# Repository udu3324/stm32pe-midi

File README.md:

# stm32pe-midi controller

An expressive midi controller based on the stm32 ecosystem. It uses the MPE midi protocol to pass through signals that act as gestures/effects including velocity/note to any music DAW. (like ableton)

 - Uses the powerful STM32H7
 - Uses USB-C OTG to connect to a device
 - Has per key PWM leds for indication
 - Low profile/one sided pcb design
 - Small key footprint for compactness
 - Two octaves + extra key before an octave

See it in action [here](https://www.youtube.com/watch?v=022ZFJn4nkc)!

# Why I Made It

This controller will be able to make music more accessible by being more affordable to the typical person. Most MPE midi controllers on the market cost between [$500 USD to $2000](https://www.expressivee.com/2-osmose). I also made this project to touch the stm32 ecosystem and learn how to integrate and use it. This midi keyboard could also make my workflow nicer for making music in Ableton.

# Design

To reduce the cost of production, I decided to design a compliant mechanism (flexure) that would be only one part. It would reduce the labor and cost by a lot. This is because most keyboards/pianos have between 10 to 100 which I have reduced to a minimum of 2. A hall effect sensor is used to measure the position and rotation of a magnet embedded in each key.

# Problems

There were many problems while prototyping and laying out things. I had bare knowledge of how flexures worked and had to create as many prototypes as needed until the right movement was made. I also didn't know that the size of the board would be a big constraint that was completely ignored.

**I highly recommend to look over these issues before building another stm32pe device!!!**
A lot of tolerances for the 3d prints are based on my 3d-printer. Make sure to print segments before making the entire thing to test for fit between the pcb, magnet, and everything.

Problems during fabrication
 * TMAG5273 has a fixed i2c address which only differs by buying different models (B1, C1, D1) or by running extra interrupt traces
 * M screw spacers broke off when screwing into plastic
 * Too high of a tolerance between the board and 3d printed parts, had to cut off bottom two aligners on all keys
 * Connection (led mux) from main-board to other board was made through really tiny & painful to solder wires

Here's a list of problems after fabrication + firmware
 * The Black key flexure design suffers too much with plastic deformation permanently, as well as temporarily
 * ^ This issue also causes a permanent distance change with less distance to measure and use
 * TMAG5273 library has no calibration feature and the measured angle is offset when brought closer
 * Keys are a bit too slippery and need a dimple to grip the finger
 * Flexures on both key types are a little on the firm side, takes a little time to get used to
 * Last white key (b) is impractical as header wires are blocking its roll to pitch change up
 * The power on led is a bit too bright, not changeable
 * The base/case of the stm32h7 is kinda slippery
 * PLA flexures can get deformed under heat in a car which can leave a permanent loss of height on keys or mess more with the already high tolerance to allow press fitting

These issues do not make the stm32pe midi keyboard worthless or horrible to use, but are just little tiny problems that could be polished in the future.

# Firmware

 * [tinyusb lib](https://github.com/hathach/tinyusb) on MIT license
 * [i2c-mux stm32 lib](https://github.com/jtainer/i2c-mux) on BSD-2-Clause license
 * [stm32 tmag5273 lib](https://github.com/devOramaMan/stm32_TMAG5273) on No license (added a i2c address rewrite based on the datasheet as well as a crucial fix)

Thank you to all the open source libraries above to make this project possible. I don't think I would have the expertise to implement all my ics this well.

The firmware for the stm32pe midi controller is written in c/cpp on stm32cubeide and flashed with stm32cubeprogrammer. Amazing platform. Outdated UI (lol). **To be as transparent as possible**, some of the firmware was written/assisted with AI. About 20% of it was written mostly with AI, while the rest + logic that ties everything together was me. `mpe.c`, 80% of `helper.c`, 60% of `tlc5940.c`, and 5% of `main.c` with some fixes to `TMAG5273.c` was assisted with AI. I do understand what the firmware does. Depending on your perspective on AI, it shouldn't really matter as I know what I'm doing. 

All of the code is stored in `firmware/stm32pe_midi/Core/Src` or `/Core/Inc`. `Src/main.c` contains some user preferences that can be set through variables.

```c
//midi
int start_octave = 4; //midi code shift
int mt_send_black = 40; //midi on threshold
int mt_send_white = 30; //midi on threshold

//mpe
int16_t pitch_mpe_st = 682; //mpe semitone pitch range (682 = 4st, 341 = 2st)
float angle_mpe_padding = 15; //mpe pitch
float angle_mpe_realistic_max = 25; //mpe pitch

float aftertouch_mpe_white_padding = 9; //mpe aftertouch
float aftertouch_mpe_black_padding = 15; //mpe aftertouch

//octave
uint32_t octave_change_mode_time_threshold = 200; //diff change between mode/octive
uint32_t octave_led_flash = 500; //ms between led flash during mode

//led
int startup_cutoff_wait = 100; //led cutoff + cutoff for initial sensor readings saving

//mode
uint32_t octave_mode_hold_down = 1500; //octave mode keys milliseconds to hold down & change
uint32_t mpe_mode_hold_down = 3000; //~ same above but for mpe mode keys

//debug
bool disable_comport = false; //silences comport to possibly make processing faster?
```

# Wiring

# BOM
This is an approximate bill of materials that is a little flexible. It would be around $333.27, ±5 dollars in case of shipping or extra taxes/fees. Thank you Hack Club - Highway for funding this.

| Part                       | Cost         | Count | Supplier | Note                                                           | Link                                                                                            |
|----------------------------|--------------|-------|----------|----------------------------------------------------------------|-------------------------------------------------------------------------------------------------|
| PLA Filament (white)       | $16.99       | 1     | Amazon   | I have a 3d printer and would like to print most of the parts. | [https://www.amazon.com/dp/B07PGZNM34](https://www.amazon.com/dp/B07PGZNM34)                    |
| PLA Filament (black)       | $16.99       | 1     | Amazon   | ~ (for the black keys)                                         | [https://www.amazon.com/dp/B07PGY2JP1](https://www.amazon.com/dp/B07PGY2JP1)                    |
| UV Plastic Glue            | $14.15       | 1     | Amazon   | This is for the underside of the keys to stop scraping.        | [https://www.amazon.com/dp/B00QU5M4VW](https://www.amazon.com/dp/B00QU5M4VW)                    |
| Header 10 Pins             | $0.78        | 2     | DigiKey  | (does not include shipping/taxes)                              | [68000-110HLF](https://www.digikey.com/en/products/detail/amphenol-cs-fci/68000-110HLF/1878503) |
| Header 5 Pins              | $0.63        | 1     | DigiKey  | ~                                                              | [68000-105HLF](https://www.digikey.com/en/products/detail/amphenol-cs-fci/68000-105HLF/2023304) |
| PCB Fabrication + Assembly | $151.09      | 2     | JLCPCB   | *no coupons applied yet                                        |                                                                                                 |
| PCB Shipping               | $33.52       | n/a   | ~        |                                                                |                                                                                                 |
| Customs duties & taxes     | $83.10       | n/a   | ~        |                                                                |                                                                                                 |
| Sales Tax                  | $15.24       | n/a   | ~        |                                                                |                                                                                                 |
| TOTAL                      | $333.27      |       |          |                                                                |                                                                                                 |

I forgot to add two more parts to the bom. They have been covered out of pocket which is fine

| Part                  | Cost    | Count | Supplier | Note                                                                                                                                                         | Link                                                                                                         |
|-----------------------|---------|-------|----------|--------------------------------------------------------------------------------------------------------------------------------------------------------------|--------------------------------------------------------------------------------------------------------------|
| 5mm Cube Magnets      | $16.99  | 45    | Amazon   | I could not find any listings with lower quantities                                                                                                          | [https://www.amazon.com/dp/B0CW9GVTX2](https://www.amazon.com/dp/B0CW9GVTX2)                                 |
| M3 5mm Screws         | ¥2.14   | 50    | Taobao   | Pretty cheap! (30 cents usd)                                                                                                                                 | [https://detail.tmall.com/item.htm?id=722759297726](https://detail.tmall.com/item.htm?id=722759297726)       |
| Female 10pin Headers  | $5.62   | 1     | Mouser   | This is for the main board. The part itself **costs $0.63 without taxes/shipping.**                                                                          | [https://www.mouser.com/ProductDetail/710-61301011821](https://www.mouser.com/ProductDetail/710-61301011821) |
| JLCPCB Two Design Fee | $38.99  | n/a   | JLCPCB   | 😭 i did not think about this while designing, i tried negotiating and doing everything                                                                      |                                                                                                              |
| TMAG5273-B1/C1/D1     | $23.28  | 18    | Mouser   | i stg the datasheet said the sensor's i2c addresses were reprogrammable.. but they didn't say i needed to hookup interrupts to them too... lesson learned :p |                                                                                                              |
| Total out of pocket   | $85.18  |       |          |                                                                                                                                                              |                                                                                                              |
| REAL TOTAL            | $418.45 |       |          |                                                                                                                                                              |                                                                                                              |

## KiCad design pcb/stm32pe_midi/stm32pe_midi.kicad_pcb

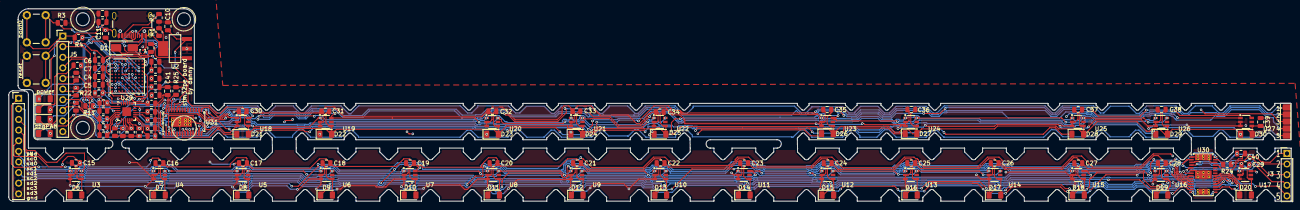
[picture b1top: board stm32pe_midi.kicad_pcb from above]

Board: 4 copper layers, 307.0 x 46.1 mm, 135 parts (0 on the bottom side), 83 nets.

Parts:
C1, C2: 2.2μF; C_0805_2012Metric
C3, C5: 4.7μF; C_0805_2012Metric
C4, C6, C7, C9, C12: 100nF; C_0805_2012Metric
C8, C13, C14: 1μF; C_0805_2012Metric
C10: 33μF; C_0805_2012Metric
C11: 0.47μF; C_0805_2012Metric
C15, C16, C17, C18, C19, C20, C21, C22, C23, C24, C25, C26, C27, C28, C29, C30, C31, C32, C33, C34, C35, C36, C37, C38, C39, C40, C41: 0.1μF; C_0805_2012Metric
D1: SS14; D_SMA
D3, D4, D5, D33: LED; LED_1206_3216Metric
D6, D7, D8, D9, D10, D11, D12, D13, D14, D15, D16, D17, D18, D19, D20, D21, D22, D23, D24, D25, D26, D27, D28, D29, D30: LED_Small; LED_1206_3216Metric
J1: USB4105; USB_C_Receptacle_GCT_USB4105-xx-A_16P_TopMnt_Horizontal
J3: Conn_01x05_Pin; PinHeader_1x05_P2.54mm_Vertical
J4: Conn_01x10_Pin; PinHeader_1x10_P2.54mm_Vertical
J5: Conn_01x10_Socket; PinHeader_1x10_P2.54mm_Vertical
J6: Conn_01x05_Pin; custom_pads
R1, R2, R24, R25: 5.1kΩ; R_0805_2012Metric
R3, R4: 10kΩ; R_0805_2012Metric
R5, R6, R7, R27: 330Ω; R_0805_2012Metric
R8, R9, R10, R11, R12, R13, R14, R15, R16, R17, R18, R19, R20, R21, R22, R23: 2.2kΩ; R_0805_2012Metric
SW1, SW2: SW_SPST; SW_PUSH_6mm
U1: STM32H743VIHx; TFBGA-100_8x8mm_Layout10x10_P0.8mm
U2: LM3940IMPX-3.3/NOPB; SOT-223-4_L6.5-W3.5-P2.30-LS7.0-BR
U3, U4, U5, U6, U7, U8, U9, U10, U11, U12, U13, U14, U15, U16, U17, U18, U19, U20, U21, U22, U23, U24, U25, U26, U27: TMAG5273; SOT-23-6_L2.9-W1.6-P0.95-LS2.8-BR
U28: TPD2EUSB30; Texas_DRT-3
U29: TCA9548A; Texas_RGE0024C_VQFN-24-1EP_4x4mm_P0.5mm_EP2.1x2.1mm
U30, U31: TLC5940PWP; HTSSOP-28-1EP_4.4x9.7mm_P0.65mm_EP3.4x9.5mm_Mask2.4x6.17mm_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

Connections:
3v3: C4.2, C5.2, C6.2, C7.2, C10.1, C12.1, C13.1, C15.2, C16.2, C17.2, C18.2, C19.2, C20.2, C21.2, C22.2, C23.2, C24.2, C25.2, C26.2, C27.2, C28.2, C29.2, C30.2, C31.2, C32.2, C33.2, C34.2, C35.2, C36.2, C37.2, C38.2, C39.2, C40.2, C41.2, D3.2 (A), D6.2 (A), D7.2 (A), D8.2 (A), D9.2 (A), D10.2 (A), D11.2 (A), D12.2 (A), D13.2 (A), D14.2 (A), D15.2 (A), D16.2 (A), D17.2 (A), D18.2 (A), D19.2 (A), D20.2 (A), D21.2 (A), D22.2 (A), D23.2 (A), D24.2 (A), D25.2 (A), D26.2 (A), D27.2 (A), D28.2 (A), D29.2 (A), D30.2 (A), J4.1, J5.1, R4.1, R8.2, R9.2, R10.2, R11.2, R12.2, R13.2, R14.2, R15.2, R16.2, R17.2, R18.2, R19.2, R20.2, R21.2, R22.2, R23.2, SW1.2 (B), U1.B2 (VBAT), U1.D2 (VDD), U1.F5 (VDD), U1.F6 (VDD33_USB), U1.K1 (VDD), U2.3 (OUT), U3.4 (VCC), U4.4 (VCC), U5.4 (VCC), U6.4 (VCC), U7.4 (VCC), U8.4 (VCC), U9.4 (VCC), U10.4 (VCC), U11.4 (VCC), U12.4 (VCC), U13.4 (VCC), U14.4 (VCC), U15.4 (VCC), U16.4 (VCC), U17.4 (VCC), U18.4 (VCC), U19.4 (VCC), U20.4 (VCC), U21.4 (VCC), U22.4 (VCC), U23.4 (VCC), U24.4 (VCC), U25.4 (VCC), U26.4 (VCC), U27.4 (VCC), U29.21 (VCC), U30.28 (VCC), U31.28 (VCC)
5v: C11.1, C14.2, U2.1 (IN)
BLANK: J6.2, U1.K2 (PA3), U31.2 (BLANK)
BOOT0: R3.2, SW1.1 (A), U1.D5 (BOOT0)
GND: C1.1, C2.1, C3.1, C4.1, C5.1, C6.1, C7.1, C8.1, C9.1, C10.2, C11.2, C12.2, C13.2, C15.1, C16.1, C17.1, C18.1, C19.1, C20.1, C21.1, C22.1, C23.1, C24.1, C25.1, C26.1, C27.1, C28.1, C29.1, C30.1, C31.1, C32.1, C33.1, C34.1, C35.1, C36.1, C37.1, C38.1, C39.1, C40.1, C41.1, J1.A1 (GND), J1.A12 (GND), J1.B1 (GND), J1.B12 (GND), J1.S1 (SHIELD), J4.10, J5.10, R1.2, R2.1, R3.1, R5.1, R6.1, R7.1, R24.1, R25.1, R27.1, SW2.2 (B), U1.C2 (VSS), U1.E4 (VSS), U1.E5 (VSS), U1.E6 (VSS), U1.G1 (VSSA), U1.J1 (VSS), U2.2 (GND), U2.4 (GND), U3.2 (GND), U3.3 (GND(TEST)), U4.2 (GND), U4.3 (GND(TEST)), U5.2 (GND), U5.3 (GND(TEST)), U6.2 (GND), U6.3 (GND(TEST)), U7.2 (GND), U7.3 (GND(TEST)), U8.2 (GND), U8.3 (GND(TEST)), U9.2 (GND), U9.3 (GND(TEST)), U10.2 (GND), U10.3 (GND(TEST)), U11.2 (GND), U11.3 (GND(TEST)), U12.2 (GND), U12.3 (GND(TEST)), U13.2 (GND), U13.3 (GND(TEST)), U14.2 (GND), U14.3 (GND(TEST)), U15.2 (GND), U15.3 (GND(TEST)), U16.2 (GND), U16.3 (GND(TEST)), U17.2 (GND), U17.3 (GND(TEST)), U18.2 (GND), U18.3 (GND(TEST)), U19.2 (GND), U19.3 (GND(TEST)), U20.2 (GND), U20.3 (GND(TEST)), U21.2 (GND), U21.3 (GND(TEST)), U22.2 (GND), U22.3 (GND(TEST)), U23.2 (GND), U23.3 (GND(TEST)), U24.2 (GND), U24.3 (GND(TEST)), U25.2 (GND), U25.3 (GND(TEST)), U26.2 (GND), U26.3 (GND(TEST)), U27.2 (GND), U27.3 (GND(TEST)), U28.3 (GND), U29.9 (GND), U29.18 (A2), U29.22 (A0), U29.23 (A1), U30.1 (GND), U30.6 (VPRG), U30.26 (DCPRG), U30.29 (PAD), U31.1 (GND), U31.6 (VPRG), U31.26 (DCPRG), U31.29 (PAD)
GSCLK: J6.1, U1.H2 (PA1), U31.25 (GSCLK)
I2C1_SCL: R23.1, U1.B5 (PB6), U29.19 (SCL)
I2C1_SDA: R22.1, U1.A5 (PB7), U29.20 (SDA)
MPRESET: U1.B4 (PB8), U29.24 (~RESET)
NRST: R4.2, SW2.1 (A), U1.E1 (NRST)
unnamed: C1.2, U1.E7 (VCAP)
unnamed: C2.2, U1.F8 (VCAP)
unnamed: D1.2 (A), J1.A4 (VBUS), J1.A9 (VBUS), J1.B4 (VBUS), J1.B9 (VBUS)
unnamed: C14.1, D1.1 (K)
unnamed: D3.1 (K), R5.2
unnamed: D4.1 (K), R6.2
unnamed: D5.1 (K), R7.2
unnamed: D6.1 (K), U30.7 (OUT0)
unnamed: D7.1 (K), U30.8 (OUT1)
unnamed: D8.1 (K), U30.9 (OUT2)
unnamed: D9.1 (K), U30.10 (OUT3)
unnamed: D10.1 (K), U30.11 (OUT4)
unnamed: D11.1 (K), U30.12 (OUT5)
unnamed: D12.1 (K), U30.13 (OUT6)
unnamed: D13.1 (K), U30.14 (OUT7)
unnamed: D14.1 (K), U30.15 (OUT8)
unnamed: D15.1 (K), U30.16 (OUT9)
unnamed: D16.1 (K), U30.17 (OUT10)
unnamed: D17.1 (K), U30.18 (OUT11)
unnamed: D18.1 (K), U30.19 (OUT12)
unnamed: D19.1 (K), U30.20 (OUT13)
unnamed: D20.1 (K), U30.21 (OUT14)
unnamed: D21.1 (K), U31.7 (OUT0)
unnamed: D22.1 (K), U31.8 (OUT1)
unnamed: D23.1 (K), U31.9 (OUT2)
unnamed: D24.1 (K), U31.10 (OUT3)
unnamed: D25.1 (K), U31.11 (OUT4)
unnamed: D26.1 (K), U31.12 (OUT5)
unnamed: D27.1 (K), U31.13 (OUT6)
unnamed: D28.1 (K), U31.14 (OUT7)
unnamed: D29.1 (K), U31.15 (OUT8)
unnamed: D30.1 (K), U31.16 (OUT9)
unnamed: D33.1 (K), R27.2
unnamed: J1.A5 (CC1), R1.1
unnamed: J1.B5 (CC2), R2.2
unnamed: J3.1, U30.25 (GSCLK)
unnamed: J3.2, U30.2 (BLANK)
unnamed: J3.3, U30.3 (XLAT)
unnamed: J3.4, U30.4 (SCLK)
unnamed: J3.5, U30.5 (SIN)
unnamed: J5.2, R9.1, U29.2 (SC0)
unnamed: J5.3, R8.1, U29.1 (SD0)
unnamed: J5.4, R10.1, U29.4 (SC1)
unnamed: J5.5, R11.1, U29.3 (SD1)
unnamed: J5.6, R12.1, U29.6 (SC2)
unnamed: J5.7, R13.1, U29.5 (SD2)
unnamed: J6.5, U31.24 (SOUT)
unnamed: C8.2, C9.2, U1.H1 (VDDA)
unnamed: C3.2, U1.F4 (VDDLDO)
unnamed: R24.2, U30.27 (IREF)
unnamed: R25.2, U31.27 (IREF)
OTG_FS_DM: J1.A7 (D-), J1.B7 (D-), U1.C10 (PA11), U28.2 (D-)
OTG_FS_DP: J1.A6 (D+), J1.B6 (D+), U1.B10 (PA12), U28.1 (D+)
PA8: D33.2 (A), U1.D9 (PA8)
SC0: J4.2, U3.1 (SCL), U4.1 (SCL), U5.1 (SCL), U6.1 (SCL)
SC1: J4.4, U7.1 (SCL), U8.1 (SCL), U9.1 (SCL), U10.1 (SCL)
SC2: J4.6, U11.1 (SCL), U12.1 (SCL), U13.1 (SCL), U14.1 (SCL)
SC3: J4.8, J5.8, R14.1, U15.1 (SCL), U16.1 (SCL), U17.1 (SCL), U18.1 (SCL), U29.8 (SC3)
SC4: R16.1, U19.1 (SCL), U20.1 (SCL), U21.1 (SCL), U22.1 (SCL), U29.11 (SC4)
SC5: R18.1, U23.1 (SCL), U24.1 (SCL), U25.1 (SCL), U26.1 (SCL), U29.13 (SC5)
SC6: R20.1, U27.1 (SCL), U29.15 (SC6)
SCLK: J6.4, U1.H3 (PA5), U31.4 (SCLK)
SD0: J4.3, U3.6 (SDA), U4.6 (SDA), U5.6 (SDA), U6.6 (SDA)
SD1: J4.5, U7.6 (SDA), U8.6 (SDA), U9.6 (SDA), U10.6 (SDA)
SD2: J4.7, U11.6 (SDA), U12.6 (SDA), U13.6 (SDA), U14.6 (SDA)
SD3: J4.9, J5.9, R15.1, U15.6 (SDA), U16.6 (SDA), U17.6 (SDA), U18.6 (SDA), U29.7 (SD3)
SD4: R17.1, U19.6 (SDA), U20.6 (SDA), U21.6 (SDA), U22.6 (SDA), U29.10 (SD4)
SD5: R19.1, U23.6 (SDA), U24.6 (SDA), U25.6 (SDA), U26.6 (SDA), U29.12 (SD5)
SD6: R21.1, U27.6 (SDA), U29.14 (SD6)
SIN: U1.K3 (PA7), U31.5 (SIN)
USART1_RX: D5.2 (A), U1.D10 (PA10)
USART1_TX: D4.2 (A), U1.C9 (PA9)
XLAT: J6.3, U1.J2 (PA2), U31.3 (XLAT)

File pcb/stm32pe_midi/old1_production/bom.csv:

Designator,Footprint,Quantity,Value,LCSC Part #
"C1, C2",0805,2,2.2μF,
C10,0805,1,33μF,
C11,0805,1,0.47μF,
"C12, C4, C6, C7, C9",0805,5,100nF,
"C13, C14, C8",0805,3,1μF,
"C15, C16, C17, C18, C19, C20, C21, C22, C23, C24, C25, C26, C27, C28, C29, C30, C31, C32, C33, C34, C35, C36, C37, C38, C39, C40, C41",0805,27,0.1μF,
"C3, C5",0805,2,4.7μF,
D1,D_SMA,1,SS14,
"D10, D11, D12, D13, D14, D15, D16, D17, D18, D19, D20, D21, D22, D23, D24, D25, D26, D27, D28, D29, D30, D6, D7, D8, D9",1206,25,LED_Small,
D2,D_SOD-882,1,PESD5V0S1UL,
"D3, D33, D4, D5",1206,4,LED,
J1,USB_C_Receptacle_GCT_USB4105-xx-A_16P_TopMnt_Horizontal,1,USB_C_Receptacle_USB2.0_16P,
J3,PinHeader_1x05_P2.54mm_Vertical,1,Conn_01x05_Pin,
J4,PinHeader_1x10_P2.54mm_Vertical,1,Conn_01x10_Pin,
J5,PinHeader_1x10_P2.54mm_Vertical,1,Conn_01x10_Socket,
J6,custom_pads,1,Conn_01x05_Pin,
"MOUSE-BITE-2MM-SLOT-1, MOUSE-BITE-2MM-SLOT-2, MOUSE-BITE-2MM-SLOT-3, MOUSE-BITE-2MM-SLOT-4, MOUSE-BITE-2MM-SLOT-5",mouse-bite-2mm-slot,5,VAL**,
"R1, R2, R24, R25",0805,4,5.1kΩ,
"R10, R11, R12, R13, R14, R15, R16, R17, R18, R19, R20, R21, R22, R23, R8, R9",0805,16,2.2kΩ,
"R27, R5, R6, R7",0805,4,330Ω,
"R3, R4",0805,2,10kΩ,
"SW1, SW2",SW_PUSH_6mm,2,SW_SPST,
U1,TFBGA-100_8x8mm_Layout10x10_P0.8mm,1,STM32H743VIHx,
"U10, U11, U12, U13, U14, U15, U16, U17, U18, U19, U20, U21, U22, U23, U24, U25, U26, U27, U3, U4, U5, U6, U7, U8, U9",SOT-23-6_L2.9-W1.6-P0.95-LS2.8-BR,25,TMAG5273,C3716049
U2,SOT-223-4_L6.5-W3.5-P2.30-LS7.0-BR,1,LM3940IMPX-3.3/NOPB,C544820
U28,Texas_DRT-3,1,TPD2EUSB30,
U29,Texas_RGE0024C_VQFN-24-1EP_4x4mm_P0.5mm_EP2.1x2.1mm,1,TCA9548A,
"U30, U31",HTSSOP-28-1EP_4.4x9.7mm_P0.65mm_EP3.4x9.5mm_Mask2.4x6.17mm_ThermalVias,2,TLC5940PWP,

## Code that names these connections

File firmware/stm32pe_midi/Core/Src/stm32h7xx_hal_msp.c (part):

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
    __HAL_RCC_GPIOB_CLK_ENABLE();
    /**I2C1 GPIO Configuration
    PB7     ------> I2C1_SDA
    PB6     ------> I2C1_SCL
    */
    GPIO_InitStruct.Pin = GPIO_PIN_7|GPIO_PIN_6;
    GPIO_InitStruct.Mode = GPIO_MODE_AF_OD;
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    __HAL_RCC_I2C1_CLK_DISABLE();

    /**I2C1 GPIO Configuration
    PB7     ------> I2C1_SDA
    PB6     ------> I2C1_SCL
    */
    HAL_GPIO_DeInit(GPIOB, GPIO_PIN_7);

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
    __HAL_RCC_GPIOA_CLK_ENABLE();
    /**SPI1 GPIO Configuration
    PA5     ------> SPI1_SCK
    PA7     ------> SPI1_MOSI
    */
    GPIO_InitStruct.Pin = GPIO_PIN_5|GPIO_PIN_7;
    GPIO_InitStruct.Mode = GPIO_MODE_AF_PP;
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    __HAL_RCC_SPI1_CLK_DISABLE();

    /**SPI1 GPIO Configuration
    PA5     ------> SPI1_SCK
    PA7     ------> SPI1_MOSI
    */
    HAL_GPIO_DeInit(GPIOA, GPIO_PIN_5|GPIO_PIN_7);

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
    __HAL_RCC_GPIOA_CLK_ENABLE();
    /**TIM2 GPIO Configuration
    PA1     ------> TIM2_CH2
    */
    GPIO_InitStruct.Pin = GPIO_PIN_1;
    GPIO_InitStruct.Mode = GPIO_MODE_AF_PP;
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
    __HAL_RCC_GPIOA_CLK_ENABLE();
    /**USB_OTG_FS GPIO Configuration
    PA12     ------> USB_OTG_FS_DP
    PA11     ------> USB_OTG_FS_DM
    */
    GPIO_InitStruct.Pin = GPIO_PIN_12|GPIO_PIN_11;
    GPIO_InitStruct.Mode = GPIO_MODE_AF_PP;
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    __HAL_RCC_USB_OTG_FS_CLK_DISABLE();

    /**USB_OTG_FS GPIO Configuration
    PA12     ------> USB_OTG_FS_DP
    PA11     ------> USB_OTG_FS_DM
    */
    HAL_GPIO_DeInit(GPIOA, GPIO_PIN_12|GPIO_PIN_11);

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
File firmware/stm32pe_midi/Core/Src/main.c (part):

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/* Private user code ---------------------------------------------------------*/
/* USER CODE BEGIN 0 */

i2c_mux_t tca_mux = { .hi2c = &hi2c1,     // Using I2C1 on PB6 (SCL) / PB7 (SDA)
		.rst_port = GPIOB,          // Reset pin is PB7
		.rst_pin = GPIO_PIN_8,      // Use correct GPIO pin number
		.addr_offset = 0            // 0 if all A0/A1/A2 pins are GND
		};
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  HAL_GPIO_WritePin(GPIOA, GPIO_PIN_9|GPIO_PIN_8|GPIO_PIN_10|GPIO_PIN_2
                          |GPIO_PIN_3, GPIO_PIN_RESET);

  /*Configure GPIO pin : PB8 */
  GPIO_InitStruct.Pin = GPIO_PIN_8;
  GPIO_InitStruct.Mode = GPIO_MODE_OUTPUT_PP;
  GPIO_InitStruct.Pull = GPIO_NOPULL;
  GPIO_InitStruct.Speed = GPIO_SPEED_FREQ_LOW;
  HAL_GPIO_Init(GPIOB, &GPIO_InitStruct);

  /*Configure GPIO pins : PA9 PA8 PA10 PA2
                           PA3 */
  GPIO_InitStruct.Pin = GPIO_PIN_9|GPIO_PIN_8|GPIO_PIN_10|GPIO_PIN_2
                          |GPIO_PIN_3;
  GPIO_InitStruct.Mode = GPIO_MODE_OUTPUT_PP;
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
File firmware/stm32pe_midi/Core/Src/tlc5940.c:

#include "tlc5940.h"

#define GSCLK_GPIO_Port GPIOA
#define GSCLK_Pin       GPIO_PIN_1

#define BLANK_GPIO_Port GPIOA
#define BLANK_Pin       GPIO_PIN_3

#define XLAT_GPIO_Port  GPIOA
#define XLAT_Pin        GPIO_PIN_2

//#define DEBUG_LED_GPIO_Port GPIOA
//#define DEBUG_LED_Pin GPIO_PIN_8

extern SPI_HandleTypeDef hspi1;

static uint16_t led_pwm[TLC5940_CHANNELS] = { 0 };

static void TLC5940_SendPWMData(void);
static void TLC5940_PulsePin(GPIO_TypeDef *GPIOx, uint16_t GPIO_Pin);

void TLC5940_Init(void) {
	HAL_GPIO_WritePin(GSCLK_GPIO_Port, GSCLK_Pin, GPIO_PIN_RESET);
	HAL_GPIO_WritePin(BLANK_GPIO_Port, BLANK_Pin, GPIO_PIN_SET);
	HAL_GPIO_WritePin(XLAT_GPIO_Port, XLAT_Pin, GPIO_PIN_RESET);

	for (int i = 0; i < TLC5940_CHANNELS; i++)
		led_pwm[i] = 0;

	TLC5940_Update();
}

void TLC5940_SetLED(uint8_t led_index, uint16_t brightness) {
	if (led_index >= TLC5940_USED_LEDS)
		return;

	if (brightness > TLC5940_MAX_PWM)
		brightness = TLC5940_MAX_PWM;

	led_pwm[led_index] = brightness;
}

void TLC5940_SetMappedPhysicallyLED(uint8_t logical_index, uint16_t brightness) {
	static const uint8_t mapping_table[10] = { 0, 1, 2, 3, 4, 5, 6, 7, 8, 9 };

	uint8_t physical_index;

	if (logical_index < 10) {
		physical_index = mapping_table[logical_index];
	} else if (logical_index >= 10 && logical_index <= 25) { // 10–25 to physical 16–31
		physical_index = logical_index + 6;
	} else {
		return;
	}

	TLC5940_SetLED(physical_index, brightness);
}

//# index is the physical layout, with its index pointing to the actual key layout
static const uint8_t key_to_logical_map[25] = { 10, 11, 0, 12, 1, 13, 14, 2,
			15, 3, 16, 4, 17, 18, 5, 19, 6, 20, 21, 7, 22, 8, 23, 9, 24 };

void TLC5940_SetMappedByKeyLED(uint8_t key_index, uint16_t brightness) {
	if (key_index < 25) {
		TLC5940_SetMappedPhysicallyLED(key_to_logical_map[key_index],
				brightness);
	}
}

static void TLC5940_SendPWMData(void) {
	uint8_t data[48] = { 0 }; // 32 channels × 12 bits = 384 bits = 48 bytes
	uint32_t bit_cursor = 0;

	for (int ch = TLC5940_CHANNELS - 1; ch >= 0; ch--) // 👈 FIXED: use all 32 channels
			{
		uint16_t val = led_pwm[ch] & 0x0FFF;

		for (int b = 11; b >= 0; b--) {
			if ((val >> b) & 1)
				data[bit_cursor / 8] |= (1 << (7 - (bit_cursor % 8)));

			bit_cursor++;
		}
	}

	HAL_GPIO_WritePin(BLANK_GPIO_Port, BLANK_Pin, GPIO_PIN_SET);
	HAL_SPI_Transmit(&hspi1, data, sizeof(data), HAL_MAX_DELAY);
	TLC5940_PulsePin(XLAT_GPIO_Port, XLAT_Pin);
	HAL_GPIO_WritePin(BLANK_GPIO_Port, BLANK_Pin, GPIO_PIN_RESET);
}

static void TLC5940_PulsePin(GPIO_TypeDef *GPIOx, uint16_t GPIO_Pin) {
	HAL_GPIO_WritePin(GPIOx, GPIO_Pin, GPIO_PIN_SET);
	for (volatile int i = 0; i < 20; i++)
		__NOP();
	HAL_GPIO_WritePin(GPIOx, GPIO_Pin, GPIO_PIN_RESET);
}

void TLC5940_Update(void) {
	// DEBUG: Turn on LED before sending
	//HAL_GPIO_WritePin(DEBUG_LED_GPIO_Port, DEBUG_LED_Pin, GPIO_PIN_SET);

	// Send the full PWM data for all TLC5940 chips (should send 48 bytes for 2 chips)
	TLC5940_SendPWMData();

	// DEBUG: Turn off LED after sending
	//HAL_GPIO_WritePin(DEBUG_LED_GPIO_Port, DEBUG_LED_Pin, GPIO_PIN_RESET);

	// Pulse XLAT to latch the data
	HAL_GPIO_WritePin(XLAT_GPIO_Port, XLAT_Pin, GPIO_PIN_SET);
	HAL_GPIO_WritePin(XLAT_GPIO_Port, XLAT_Pin, GPIO_PIN_RESET);
}

void TLC5940_TestPattern(void) {
	for (uint8_t i = 0; i < TLC5940_USED_LEDS; i++) {
		for (uint8_t j = 0; j < TLC5940_CHANNELS; j++)
			TLC5940_SetLED(j, (j == i) ? 1000 : 0);

		TLC5940_Update();
		HAL_Delay(200);
	}
}

void TLC5940_AllOnTest(void) {
	for (int i = 0; i < TLC5940_CHANNELS; i++)
		TLC5940_SetLED(i, 1000);

	TLC5940_Update();
}

void TLC5940_BreatheTest(void) {
	for (uint8_t i = 0; i < TLC5940_NUM_LEDS; i++) {
		// Turn all LEDs off first
		for (uint8_t j = 0; j < TLC5940_NUM_LEDS; j++) {
			TLC5940_SetMappedLED(j, 0);
		}

		for (uint16_t b = 0; b < 1000; b++) {
			TLC5940_SetMappedLED(i, b);
			TLC5940_Update();
			HAL_Delay(0.4);
		}
		for (int16_t b = 999; b > 0; b--) {
			TLC5940_SetMappedLED(i, b);
			TLC5940_Update();
			HAL_Delay(0.4);
		}

		HAL_Delay(5);
	}

	TLC5940_Update();
}

void TLC5940_BreatheAllTest(void) {
	for (uint16_t b = 0; b < 1000; b++) {
		for (uint8_t i = 0; i < TLC5940_NUM_LEDS; i++) {
			TLC5940_SetMappedLED(i, b);
		}

		TLC5940_Update();
		HAL_Delay(1);
	}

	for (int16_t b = 999; b > 0; b--) {
		for (uint8_t i = 0; i < TLC5940_NUM_LEDS; i++) {
			TLC5940_SetMappedLED(i, b);
		}

		TLC5940_Update();
		HAL_Delay(1);
	}

	HAL_Delay(5);

	TLC5940_Update();
}

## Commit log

2025-06-08 Update JOURNAL.md
    better image + wrote some stuff that i forgot to include
2025-06-11 add cad
2025-06-13 add cad files
2025-06-25 add everything
2025-06-25 add pcb 3d models
2025-06-26 add cart
2025-06-29 add jlcpcb extra info
2025-06-29 add images
2025-07-21 add wip firmware
2025-07-21 add to gitignore
2025-07-22 init my TCA9548A i2c mux
2025-07-23 add tmag lib
2025-07-24 some more stuff
2025-07-28 tmag sensor works finally
2025-07-28 optimize handle + angle readings
2025-07-28 more optimizations
2025-07-29 add tinyusb midi implementation
2025-07-29 added tinyusb cdc, removed some debug
2025-07-30 add velocity calculations
2025-07-30 stl and images
2025-08-01 add address rewriting
2025-08-01 all keys/sensors implemented
2025-08-01 code cleanup
2025-08-01 edit readme
2025-08-01 move things to helper.c + code cleanup
2025-08-01 velocity fully works
2025-08-02 add octave change mode
2025-08-03 add mpe pitch + aftertouch + tuning
2025-08-03 add way to disable mpe midi

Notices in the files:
firmware/stm32pe_midi/Core/Src/main.c:
Copyright (c) 2025 STMicroelectronics.
All rights reserved.
This software is licensed under terms that can be found in the LICENSE file
